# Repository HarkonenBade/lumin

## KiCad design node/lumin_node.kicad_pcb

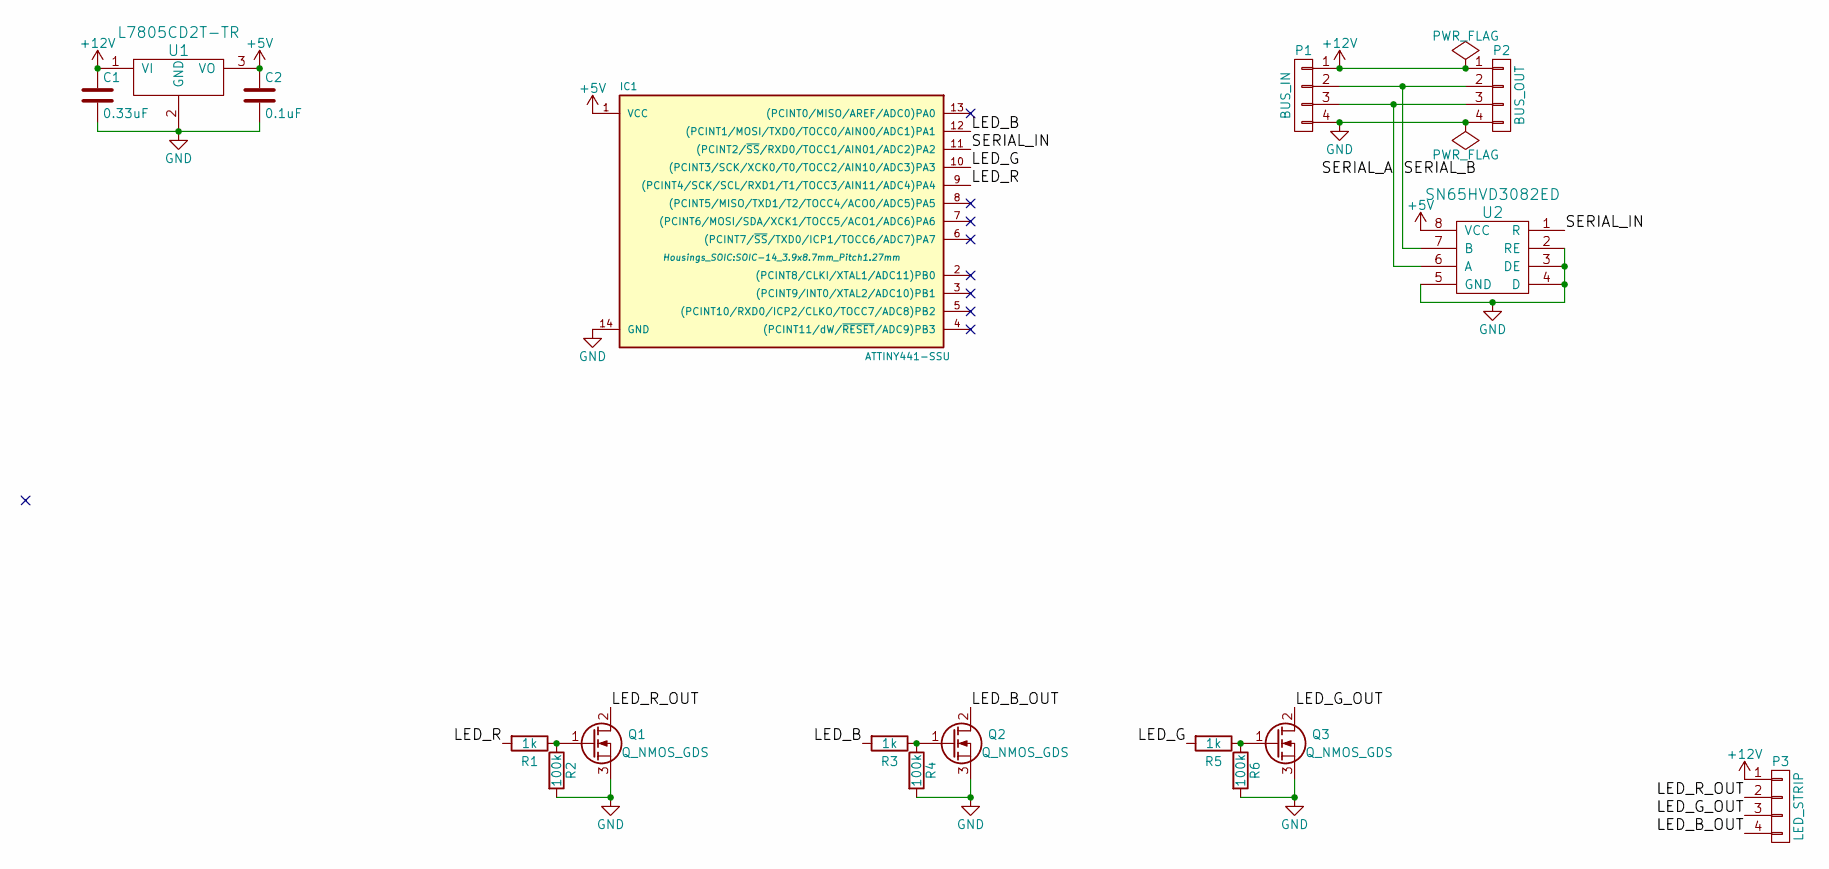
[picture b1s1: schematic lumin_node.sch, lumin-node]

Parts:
C1: 0.33uF; C_0805
C2: 0.1uF; C_0805
IC1: ATTINY441-SSU; SOIC-14_3.9x8.7mm_Pitch1.27mm; Farnell 2396716
P1: BUS_IN; Pin_Header_Straight_1x04
P2: BUS_OUT; Pin_Header_Straight_1x04
P3: LED_STRIP; Pin_Header_Straight_1x04
Q1, Q2, Q3: Q_NMOS_GDS; SuperSOT-6-123; Farnell 2322582
R1, R3, R5: 1k; R_0805
R2, R4, R6: 100k; R_0805
U1: L7805CD2T-TR; sot404; Farnell 1366576
U2: SN65HVD3082ED; SOIC-8_3.9x4.9mm_Pitch1.27mm; Farnell 8452210

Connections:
+5V: C2.1, IC1.1 (VCC), U1.3 (VO), U2.8 (VCC)
+12V: C1.1, P1.1, P2.1, P3.1, U1.1 (VI)
/LED_B: IC1.12 ((PCINT1/MOSI/TXD0/TOCC0/AIN00/ADC1)PA1), R3.2
/LED_B_OUT: P3.4, Q2.2 (D)
/LED_G: IC1.10 ((PCINT3/SCK/XCK0/T0/TOCC2/AIN10/ADC3)PA3), R5.2
/LED_G_OUT: P3.3, Q3.2 (D)
/LED_R: IC1.9 ((PCINT4/SCK/SCL/RXD1/T1/TOCC3/AIN11/ADC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), R1.2
/LED_R_OUT: P3.2, Q1.2 (D)
/SERIAL_A: P1.3, P2.3, U2.6 (A)
/SERIAL_B: P1.2, P2.2, U2.7 (B)
/SERIAL_IN: IC1.11 ((PCINT2/~SS~/RXD0/TOCC1/AIN01/ADC2)PA2), U2.1 (R)
GND: C1.2, C2.2, IC1.14 (GND), P1.4, P2.4, Q1.3 (S), Q2.3 (S), Q3.3 (S), R2.2, R4.2, R6.2, U1.2 (GND), U2.2 (RE), U2.3 (DE), U2.4 (D), U2.5 (GND)
unnamed: Q1.1 (G), R1.1, R2.1
unnamed: Q2.1 (G), R3.1, R4.1
unnamed: Q3.1 (G), R5.1, R6.1

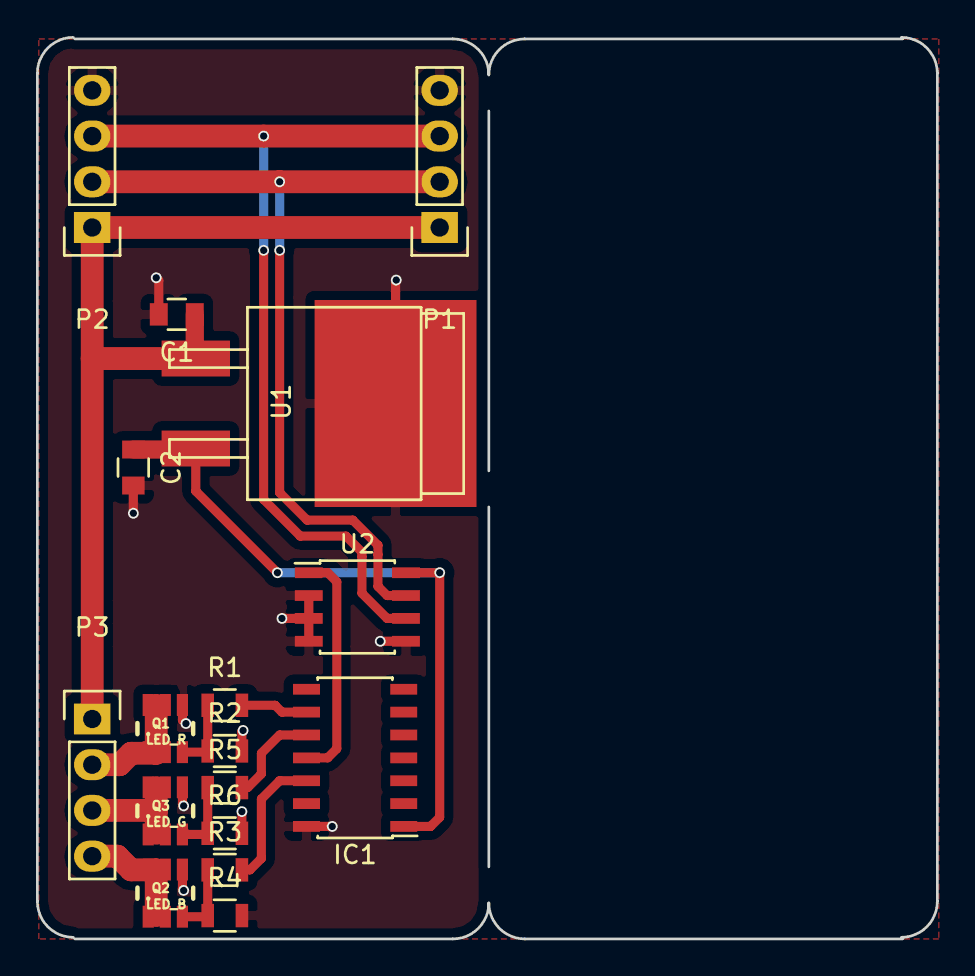
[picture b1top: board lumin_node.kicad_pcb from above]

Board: 2 copper layers, 50.0 x 50.1 mm, 17 parts (0 on the bottom side), 15 nets.

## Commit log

2015-08-20 Basic schematic
2015-08-20 Part no.s and datasheets
2015-08-20 Basic PCB design
2015-09-02 Shuffled PCB
2015-09-02 Added some TVSs
2015-09-02 Added .gitignore
